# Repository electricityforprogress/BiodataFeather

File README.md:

# BiodataFeather
Feather daughter board for the Adafruit ESP32 and Huzzah (and others), allowing BLE and RTPMIDI via wifi.
Still a work in progress, and can provide the framework for anyone to use other Adafruit Feather boards
     Lots of Biodata information on my website electricityforprogress.com
See also the project submission on [Hackaday.io](https://hackaday.io/project/182849-biodata-sonification-v05)

3D Enclosure Model: https://www.tinkercad.com/things/8HZnh0ERNtr-biodata-wifi-snap-enclosure

Menu Modes:

From normal Biodata mode, by pressing the button you will enter into the Menu selection where you can turn the knob to select different menus listed below.  When the desired menu color is illuminated click the button and continue to turn the knob to choose a value.  Click a final time to select the value and return to Biodata Mode.  Selections are saved and reloaded each time you turn on the device.  To 'hard reset' press and hold the button while turning on the device, after the light show the White led will display and the factory default settings are applied (Chromatic Scaling, Channel 1, Bluetooth ON, Wifi OFF).

Red - Note Scaling - Entering this mode will illuminate the Red LED, by turning the knob one of the other LEDs will flash indicating a different Note Scaling. Flashing Red = Chromatic, Orange = Minor, Green = Diatonic Minor, Blue = Major, White = Indian

Orange - MIDI Channel - Entering this mode will illuminate the Orange LED, by turning the knob different combinations of the LEDs are used to display the MIDI Channel in 'Binary'.  MIDI Channel can be configured between 1-16, each of the 5 LEDs are used to display the MIDI channel chosen where 1 = 1xxxx, 2 = x1xxx, 3 = 11xxx, etc. The MIDI Channel can then be saved by pressing the button.  So far, this MIDI selection method has been a big PiTA for users, but it is kinda clever.

Green - Wifi On/Off - This mode turns on and off Wifi, default is off. Control is similar to the Bluetooth mode.  If you have uploaded code with your wifi credentials, you can connect to WiFi MIDI

Blue - Bluetooth On/Off - This mode turns on and off Bluetooth, default is ON.  The Blue LED will illuminate and either the Red LED (indicating off) or White LED (indicating on) can be selected by turning the knob.  Press the button again to save the setting.

White - Battery Level - Entering into this mode will display the battery charge percentage by illuminating the white LED and one of the other colors will flash.  Flashing blue = 100%, green = 80%, Yellow = 50%, Green = 30%

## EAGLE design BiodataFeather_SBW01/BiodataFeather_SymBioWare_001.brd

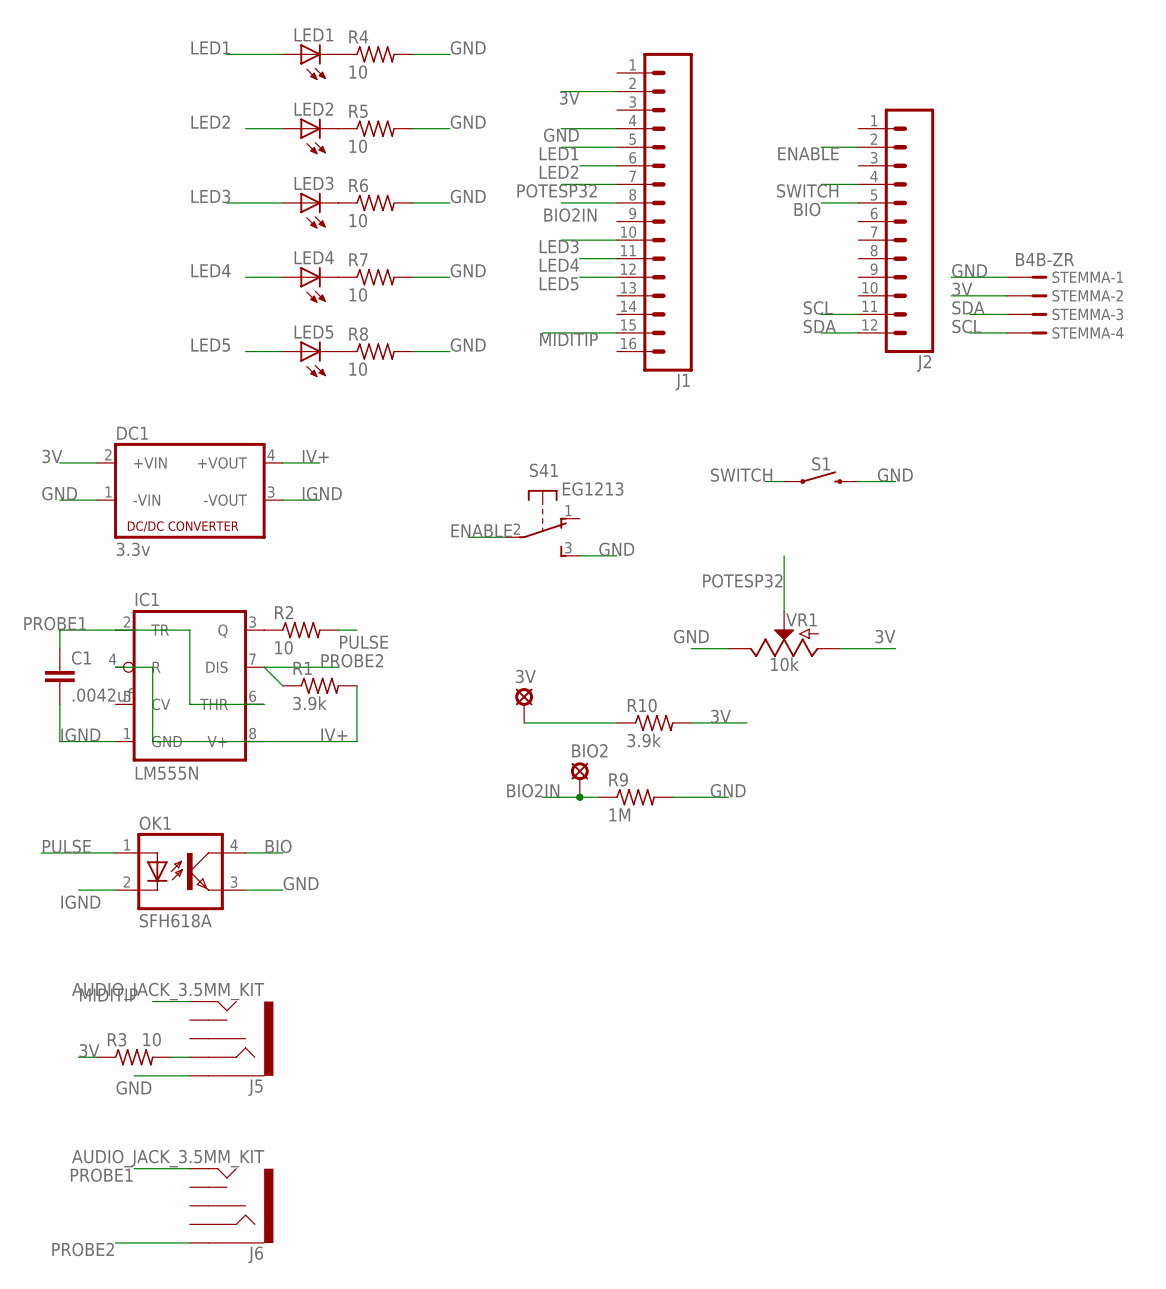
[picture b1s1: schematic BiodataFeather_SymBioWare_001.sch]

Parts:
3V: SE14
BIO2: SE14
C1: .0042uf; C2.5-2
DC1: 3.3v; NME
IC1: LM555N; DIL08
J1: CONN_161X16_NO_SILK; 1X16_NO_SILK
J2: CONN_12NO_SILK; 1X12_NO_SILK
J5, J6: AUDIO_JACK_3.5MM_KIT; AUDIO-JACK-KIT
LED1, LED2, LED3, LED4, LED5: LED5MM
OK1: SFH618A; DIP4
R1, R10: 3.9k; 0204V
R2, R3, R4, R5, R6, R7, R8: 10; 0204V
R9: 1M; 0204V
S1: MOMENTARY-SWITCH-SPST-PTH-6.0MM; TACTILE_SWITCH_PTH_6.0MM
S4: EG1213
STEMMA: B4B-ZR
VR1: 10k; POT-PTH-ALPS-KIT

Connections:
3V: DC1.2 (+VIN), J1.2, R3.1, R10.2, STEMMA.2, VR1.P$3 (A)
BIO: J2.5, OK1.4 (COL)
BIO2IN: BIO2.MP, J1.8, R9.1
ENABLE: J2.2, S4.2
GND: DC1.1 (-VIN), J1.4, J5.SLEEVE, OK1.3 (EMIT), R4.2, R5.2, R6.2, R7.2, R8.2, R9.2, S1.3 (2), S4.3 (S), STEMMA.1, VR1.P$1 (E)
IGND: C1.2, DC1.3 (-VOUT), IC1.1 (GND), OK1.2 (C)
IV+: DC1.4 (+VOUT), IC1.4 (R), IC1.8 (V+), R1.2
LED1: J1.5, LED1.A
LED2: J1.6, LED2.A
LED3: J1.10, LED3.A
LED4: J1.11, LED4.A
LED5: J1.12, LED5.A
MIDITIP: J1.15, J5.TIP
unnamed: IC1.3 (Q), R2.1
unnamed: J5.RING, R3.2
unnamed: LED1.K (C), R4.1
unnamed: 3V.MP, R10.1
unnamed: LED2.K (C), R5.1
unnamed: LED3.K (C), R6.1
unnamed: LED4.K (C), R7.1
unnamed: LED5.K (C), R8.1
POTESP32: J1.7, VR1.P$2 (S)
PROBE1: C1.1, IC1.2 (TR), IC1.6 (THR), J6.TIP
PROBE2: IC1.7 (DIS), J6.SLEEVE, R1.1
PULSE: OK1.1 (A), R2.2
SCL: J2.11, STEMMA.4
SDA: J2.12, STEMMA.3
SWITCH: J2.4, S1.1

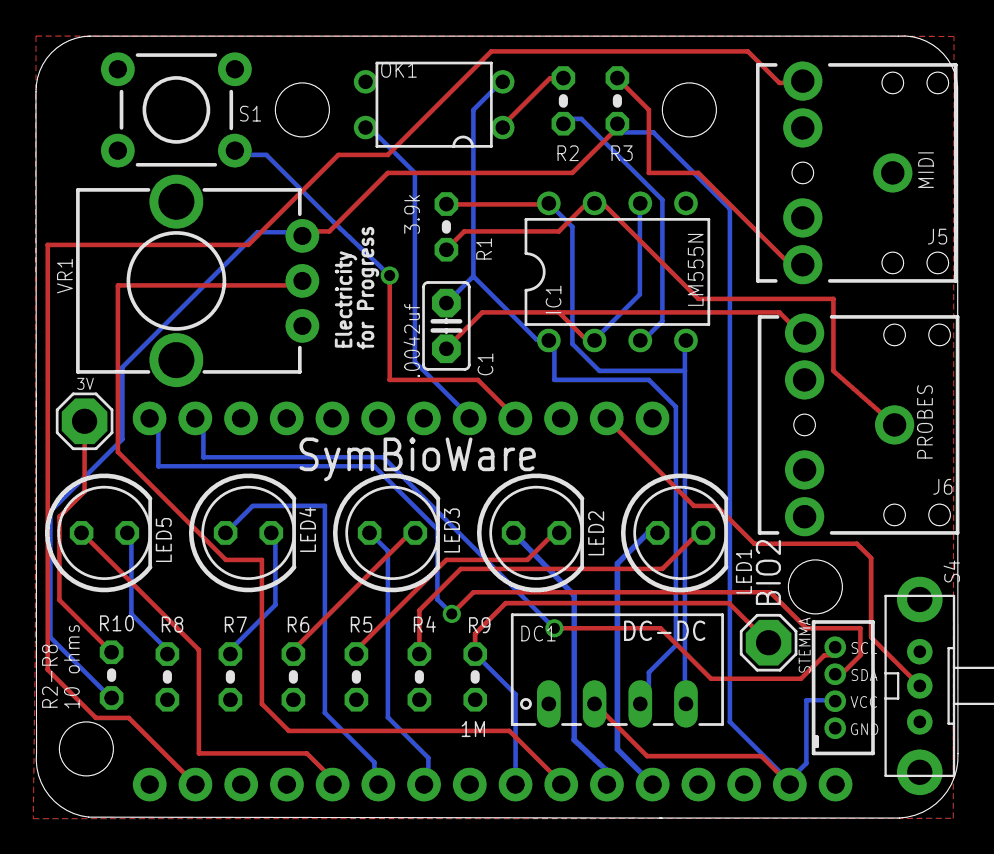
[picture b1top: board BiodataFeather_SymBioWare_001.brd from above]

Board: 2 copper layers, 51.2 x 43.4 mm, 29 parts (0 on the bottom side), 28 nets.

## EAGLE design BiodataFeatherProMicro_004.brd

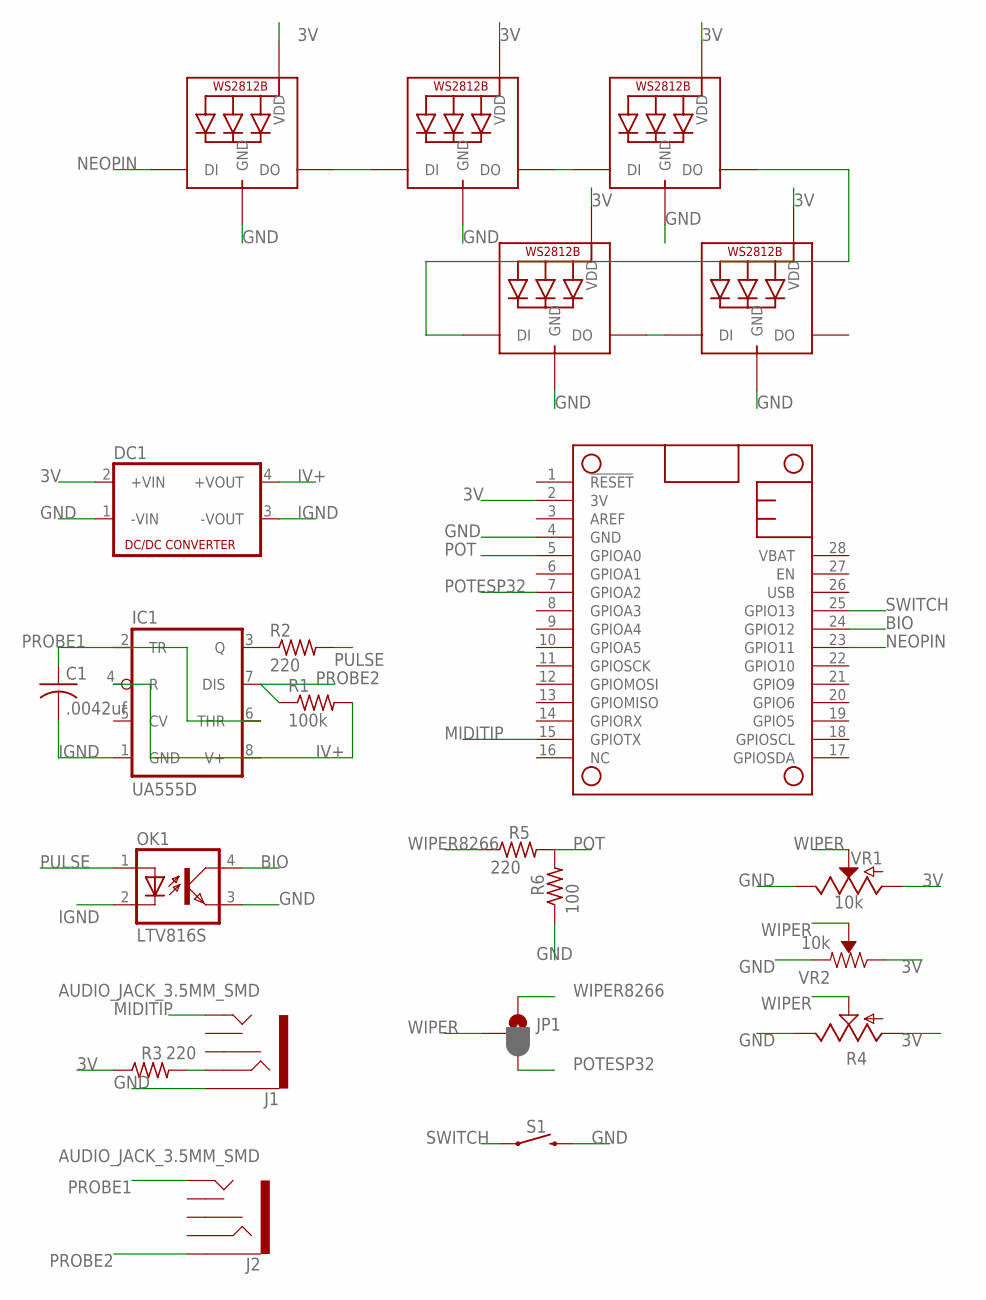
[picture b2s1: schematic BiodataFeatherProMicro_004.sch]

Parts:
C1: .0042uf; C1206
DC1: NME
IC1: UA555D; SO08
J1, J2: AUDIO_JACK_3.5MM_SMD; AUDIO-JACK-3.5MM-SMD
JP1: JUMPER-SMT_3_1-NC_PASTE_SILK; SMT-JUMPER_3_1-NC_PASTE_SILK
LED1, LED2, LED3, LED4, LED5: WS2812B5050; WS2812B
MS1: FEATHERWING; FEATHERWING_NOHOLES
OK1: LTV816S; SMD4
R1: 100k; M1206
R2, R3, R5: 220; M1206
R4: TRIM_US-S63P; S63P
R6: 100; M1206
S1: MOMENTARY-SWITCH-SPST-PTH-6.0MM; TACTILE_SWITCH_PTH_6.0MM
VR1: 10k; POT-PTH-ALPS-KIT
VR2: 10k; TRIMPOT-PTH-3386U

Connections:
3V: DC1.2 (+VIN), LED1.1-VDD (VDD), LED2.1-VDD (VDD), LED3.1-VDD (VDD), LED4.1-VDD (VDD), LED5.1-VDD (VDD), MS1.2 (3V), R3.1, R4.A, VR1.P$3 (A), VR2.3 (CW)
BIO: MS1.24 (GPIO12), OK1.4 (COL)
GND: DC1.1 (-VIN), J1.SLEEVE, LED1.3-GND (GND), LED2.3-GND (GND), LED3.3-GND (GND), LED4.3-GND (GND), LED5.3-GND (GND), MS1.4 (GND), OK1.3 (EMIT), R4.E, R6.1, S1.3 (2), VR1.P$1 (E), VR2.1 (CCW)
IGND: C1.2, DC1.3 (-VOUT), IC1.1 (GND), OK1.2 (C)
IV+: DC1.4 (+VOUT), IC1.4 (R), IC1.8 (V+), R1.2
MIDITIP: J1.TIP, MS1.15 (GPIOTX)
unnamed: IC1.3 (Q), R2.1
unnamed: J1.RING, R3.2
unnamed: LED1.2-DOUT (DO), LED2.4-DIN (DI)
unnamed: LED2.2-DOUT (DO), LED3.4-DIN (DI)
unnamed: LED4.2-DOUT (DO), LED5.4-DIN (DI)
unnamed: LED3.2-DOUT (DO), LED4.4-DIN (DI)
NEOPIN: LED1.4-DIN (DI), MS1.23 (GPIO11)
POT: MS1.5 (GPIOA0), R5.2, R6.2
POTESP32: JP1.3, MS1.7 (GPIOA2)
PROBE1: C1.1, IC1.2 (TR), IC1.6 (THR), J2.TIP
PROBE2: IC1.7 (DIS), J2.SLEEVE, R1.1
PULSE: OK1.1 (A), R2.2
SWITCH: MS1.25 (GPIO13), S1.1
WIPER: JP1.2, R4.S, VR1.P$2 (S), VR2.2 (WIPER)
WIPER8266: JP1.1, R5.1

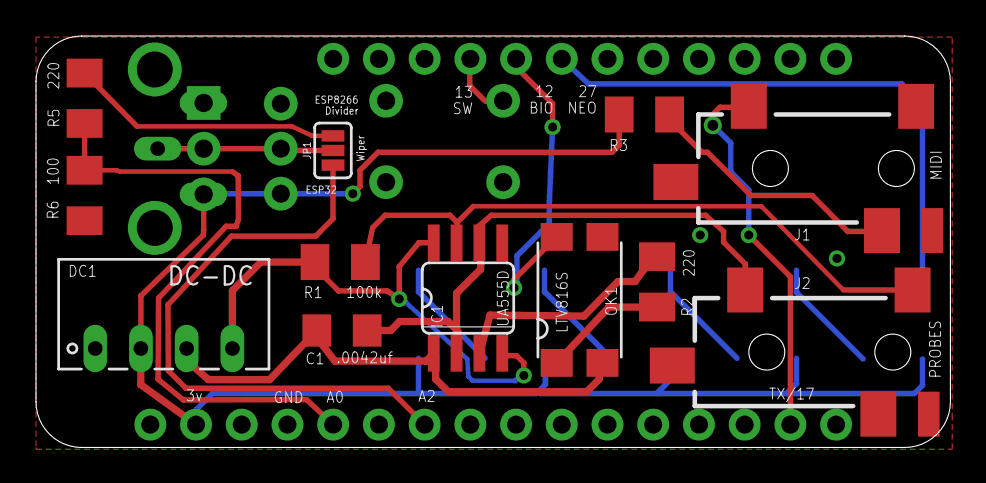
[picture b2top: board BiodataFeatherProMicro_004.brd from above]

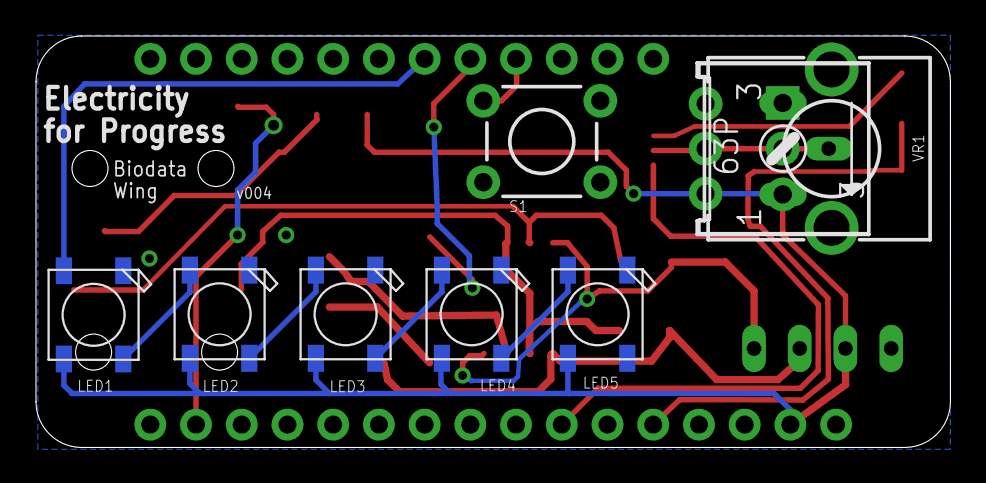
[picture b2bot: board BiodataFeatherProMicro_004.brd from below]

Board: 2 copper layers, 50.8 x 22.9 mm, 22 parts (9 on the bottom side), 21 nets.

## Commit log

2020-08-18 Initial upload
2020-08-18 Added BOM
2020-09-06 Added gerbers for Dmitriy
    These gerbers are untested ;) until my NextPCB order goes out!
2021-01-13 latest biodata wifi update
    version for Darren including blue/purple light show during wifi connection and some elements for future battery level display.
2021-04-22 changed applemidi.h
2021-10-03 Includes both BLE and Wifi, and menu modes!
2021-10-03 enclosure
2021-10-27 BLE and Wifi mode select
2021-11-08 Menu updates and reset
    modifications to the hard reset feature, hold button during boot light show and the white LED will flash indicating restore from EEPROM. On 'first upload' from a fresh ESP32 the EEPROM needs to be se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
2021-11-08 schematic
    PDF export of biodata feather schematic
2021-12-27 Create BiodataFeather_BOM
2022-01-17 Enclosure
    enclosure stls, plus 'shortie' for no header builds.
2022-03-12 comment out DBG
    commented out DBG macro print statements from AppleMIDI example code
2022-08-05 ESP32S3 with USB MIDI
    This includes USB MIDI output for an Adafruit ESP32 S3
2022-09-11 Create Biodata_v007_ESP32_S3
2022-09-11 Create USB_BLE_WIFI_MIDI
2022-09-11 Updates for USB MIDI and menu navigation
2023-05-07 Updated version with STEMMA i2C
2024-04-02 BOM
    Digikey BOM for ESP32-S3 Biodata Sonification kit, including Breadboard ;)
2024-06-24 Update Biodata_Feather_ESP32_07.ino
    updates for ledc due to espressif BREAKING changes in v3.0
2024-07-02 Update Biodata_Feather_ESP32_07.ino
    updated for ledc issues

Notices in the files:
parts and their libraries:
SparkFun-Switches: Licensing: Creative Commons ShareAlike 4.0 International - https://creativecommons.org/licenses/by-sa/4.0
